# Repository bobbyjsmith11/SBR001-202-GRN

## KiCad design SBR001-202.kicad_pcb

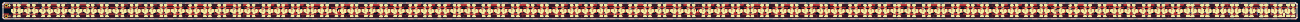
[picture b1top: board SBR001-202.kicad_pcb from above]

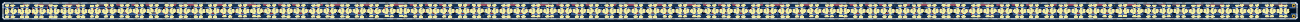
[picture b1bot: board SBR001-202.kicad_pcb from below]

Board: 2 copper layers, 895.4 x 10.9 mm, 1406 parts (703 on the bottom side), 706 nets.

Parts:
D201, D202, D203, D204, D205, D206, D207, D208, D209, D210, D211, D212, D213, D214, D215, D216, D217, D218, D219, D220, D301, D302, D303, D304, D305, D306, D307, D308, D309, D310, D311, D312, D313, D314, D315, D316, D317, D318, D319, D320, D401, D402, D403, D404, D405, D406, D407, D408, D409, D410, D411, D412, D413, D414, D415, D416, D417, D418, D419, D420, D501, D502, D503, D504, D505, D506, D507, D508, D509, D510, D511, D512, D513, D514, D515, D516, D517, D518, D519, D520, D601, D602, D603, D604, D605, D606, D607, D608, D609, D610, D611, D612, D613, D614, D615, D616, D617, D618, D619, D620, D701, D702, D703, D704, D705, D706, D707, D708, D709, D710, D711, D712, D713, D714, D715, D716, D717, D718, D719, D720, D801, D802, D803, D804, D805, D806, D807, D808, D809, D810, D811, D812, D813, D814, D815, D816, D817, D818, D819, D820, D901, D902, D903, D904, D905, D906, D907, D908, D909, D910, D911, D912, D913, D914, D915, D916, D917, D918, D919, D920, D1001, D1002, D1003, D1004, D1005, D1006, D1007, D1008, D1009, D1010, D1011, D1012, D1013, D1015, D1016, D1017, D1101, D1102, D1103, D1104, D1105, D1106, D1107, D1108, D1109, D1110, D1111, D1112, D1113, D1114, D1115, D1116, D1117, D1118, D1119, D1120, D1201, D1202, D1203, D1204, D1205, D1206, D1207, D1208, D1209, D1210, D1211, D1212, D1213, D1214, D1215, D1216, D1217, D1218, D1219, D1220, D1301, D1302, D1303, D1304, D1305, D1306, D1307, D1308, D1309, D1310, D1311, D1312, D1313, D1314, D1315, D1316, D1317, D1318, D1319, D1320, D1401, D1402, D1403, D1404, D1405, D1406, D1407, D1408, D1409, D1410, D1411, D1412, D1413, D1414, D1415, D1416, D1417, D1418, D1419, D1420, D1501, D1502, D1503, D1504, D1505, D1506, D1507, D1508, D1509, D1510, D1511, D1512, D1513, D1514, D1515, D1516, D1517, D1518, D1519, D1520, D1601, D1602, D1603, D1604, D1605, D1606, D1607, D1608, D1609, D1610, D1611, D1612, D1613, D1614, D1615, D1616, D1617, D1618, D1619, D1620, D1701, D1702, D1703, D1704, D1705, D1706, D1707, D1708, D1709, D1710, D1711, D1712, D1713, D1714, D1715, D1716, D1717, D1718, D1719, D1720, D1801, D1802, D1803, D1804, D1805, D1806, D1807, D1808, D1809, D1810, D1811, D1812, D1813, D1814, D1815, D1816, D1817, D1818, D1819, D1820, D1901, D1902, D1903, D1904, D1905, D1906, D1907, D1908, D1909, D1910, D1911, D1912, D1913, D1914, D1915, D1916: GRN; LED_0603
R201, R202, R203, R204, R205, R206, R207, R208, R209, R210, R211, R212, R237, R238, R239, R240, R241, R242, R243, R244, R301, R302, R303, R304, R305, R306, R307, R308, R309, R310, R311, R312, R337, R338, R339, R340, R341, R342, R343, R344, R401, R402, R403, R404, R405, R406, R407, R408, R409, R410, R411, R412, R437, R438, R439, R440, R441, R442, R443, R444, R501, R502, R503, R504, R505, R506, R507, R508, R509, R510, R511, R512, R537, R538, R539, R540, R541, R542, R543, R544, R601, R602, R603, R604, R605, R606, R607, R608, R609, R610, R611, R612, R637, R638, R639, R640, R641, R642, R643, R644, R701, R702, R703, R704, R705, R706, R707, R708, R709, R710, R711, R712, R737, R738, R739, R740, R741, R742, R743, R744, R801, R802, R803, R804, R805, R806, R807, R808, R809, R810, R811, R812, R837, R838, R839, R840, R841, R842, R843, R844, R901, R902, R903, R904, R905, R906, R907, R908, R909, R910, R911, R912, R937, R938, R939, R940, R941, R942, R943, R944, R1001, R1002, R1003, R1004, R1005, R1006, R1007, R1008, R1009, R1010, R1011, R1012, R1037, R1038, R1039, R1040, R1101, R1102, R1103, R1104, R1105, R1106, R1107, R1108, R1109, R1110, R1111, R1112, R1137, R1138, R1139, R1140, R1141, R1142, R1143, R1144, R1201, R1202, R1203, R1204, R1205, R1206, R1207, R1208, R1209, R1210, R1211, R1212, R1237, R1238, R1239, R1240, R1241, R1242, R1243, R1244, R1301, R1302, R1303, R1304, R1305, R1306, R1307, R1308, R1309, R1310, R1311, R1312, R1337, R1338, R1339, R1340, R1341, R1342, R1343, R1344, R1401, R1402, R1403, R1404, R1405, R1406, R1407, R1408, R1409, R1410, R1411, R1412, R1437, R1438, R1439, R1440, R1441, R1442, R1443, R1444, R1501, R1502, R1503, R1504, R1505, R1506, R1507, R1508, R1509, R1510, R1511, R1512, R1537, R1538, R1539, R1540, R1541, R1542, R1543, R1544, R1601, R1602, R1603, R1604, R1605, R1606, R1607, R1608, R1609, R1610, R1611, R1612, R1637, R1638, R1639, R1640, R1641, R1642, R1643, R1644, R1701, R1702, R1703, R1704, R1705, R1706, R1707, R1708, R1709, R1710, R1711, R1712, R1737, R1738, R1739, R1740, R1741, R1742, R1743, R1744, R1801, R1802, R1803, R1804, R1805, R1806, R1807, R1808, R1809, R1810, R1811, R1812, R1837, R1838, R1839, R1840, R1841, R1842, R1843, R1844, R1901, R1902, R1903, R1904, R1905, R1906, R1907, R1908, R1909, R1910, R1911, R1912, R1937, R1938, R1939, R1940: 442; R_0603
R213, R214, R215, R216, R217, R218, R219, R220, R221, R222, R223, R224, R225, R226, R227, R228, R229, R230, R231, R232, R233, R234, R235, R236, R245, R246, R247, R248, R249, R250, R251, R252, R253, R254, R255, R256, R257, R258, R259, R260, R313, R314, R315, R316, R317, R318, R319, R320, R321, R322, R323, R324, R325, R326, R327, R328, R329, R330, R331, R332, R333, R334, R335, R336, R345, R346, R347, R348, R349, R350, R351, R352, R353, R354, R355, R356, R357, R358, R359, R360, R413, R414, R415, R416, R417, R418, R419, R420, R421, R422, R423, R424, R425, R426, R427, R428, R429, R430, R431, R432, R433, R434, R435, R436, R445, R446, R447, R448, R449, R450, R451, R452, R453, R454, R455, R456, R457, R458, R459, R460, R513, R514, R515, R516, R517, R518, R519, R520, R521, R522, R523, R524, R525, R526, R527, R528, R529, R530, R531, R532, R533, R534, R535, R536, R545, R546, R547, R548, R549, R550, R551, R552, R553, R554, R555, R556, R557, R558, R559, R560, R613, R614, R615, R616, R617, R618, R619, R620, R621, R622, R623, R624, R625, R626, R627, R628, R629, R630, R631, R632, R633, R634, R635, R636, R645, R646, R647, R648, R649, R650, R651, R652, R653, R654, R655, R656, R657, R658, R659, R660, R713, R714, R715, R716, R717, R718, R719, R720, R721, R722, R723, R724, R725, R726, R727, R728, R729, R730, R731, R732, R733, R734, R735, R736, R745, R746, R747, R748, R749, R750, R751, R752, R753, R754, R755, R756, R757, R758, R759, R760, R813, R814, R815, R816, R817, R818, R819, R820, R821, R822, R823, R824, R825, R826, R827, R828, R829, R830, R831, R832, R833, R834, R835, R836, R845, R846, R847, R848, R849, R850, R851, R852, R853, R854, R855, R856, R857, R858, R859, R860, R913, R914, R915, R916, R917, R918, R919, R920, R921, R922, R923, R924, R925, R926, R927, R928, R929, R930, R931, R932, R933, R934, R935, R936, R945, R946, R947, R948, R949, R950, R951, R952, R953, R954, R955, R956, R957, R958, R959, R960, R1013, R1014, R1015, R1016, R1017, R1018, R1019, R1020, R1021, R1022, R1023, R1024, R1025, R1026, R1027, R1028, R1029, R1030, R1031, R1032, R1033, R1034, R1035, R1036, R1045, R1046, R1047, R1053, R1054, R1055, R1056, R1113, R1114, R1115, R1116, R1117, R1118, R1119, R1120, R1121, R1122, R1123, R1124, R1125, R1126, R1127, R1128, R1129, R1130, R1131, R1132, R1133, R1134, R1135, R1136, R1145, R1146, R1147, R1148, R1149, R1150, R1151, R1152, R1153, R1154, R1155, R1156, R1157, R1158, R1159, R1160, R1213, R1214, R1215, R1216, R1217, R1218, R1219, R1220, R1221, R1222, R1223, R1224, R1225, R1226, R1227, R1228, R1229, R1230, R1231, R1232, R1233, R1234, R1235, R1236, R1245, R1246, R1247, R1248, R1249, R1250, R1251, R1252, R1253, R1254, R1255, R1256, R1257, R1258, R1259, R1260, R1313, R1314, R1315, R1316, R1317, R1318, R1319, R1320, R1321, R1322, R1323, R1324, R1325, R1326, R1327, R1328, R1329, R1330, R1331, R1332, R1333, R1334, R1335, R1336, R1345, R1346, R1347, R1348, R1349, R1350, R1351, R1352, R1353, R1354, R1355, R1356, R1357, R1358, R1359, R1360, R1413, R1414, R1415, R1416, R1417, R1418, R1419, R1420, R1421, R1422, R1423, R1424, R1425, R1426, R1427, R1428, R1429, R1430, R1431, R1432, R1433, R1434, R1435, R1436, R1445, R1446, R1447, R1448, R1449, R1450, R1451, R1452, R1453, R1454, R1455, R1456, R1457, R1458, R1459, R1460, R1513, R1514, R1515, R1516, R1517, R1518, R1519, R1520, R1521, R1522, R1523, R1524, R1525, R1526, R1527, R1528, R1529, R1530, R1531, R1532, R1533, R1534, R1535, R1536, R1545, R1546, R1547, R1548, R1549, R1550, R1551, R1552, R1553, R1554, R1555, R1556, R1557, R1558, R1559, R1560, R1613, R1614, R1615, R1616, R1617, R1618, R1619, R1620, R1621, R1622, R1623, R1624, R1625, R1626, R1627, R1628, R1629, R1630, R1631, R1632, R1633, R1634, R1635, R1636, R1645, R1646, R1647, R1648, R1649, R1650, R1651, R1652, R1653, R1654, R1655, R1656, R1657, R1658, R1659, R1660, R1713, R1714, R1715, R1716, R1717, R1718, R1719, R1720, R1721, R1722, R1723, R1724, R1725, R1726, R1727, R1728, R1729, R1730, R1731, R1732, R1733, R1734, R1735, R1736, R1745, R1746, R1747, R1748, R1749, R1750, R1751, R1752, R1753, R1754, R1755, R1756, R1757, R1758, R1759, R1760, R1813, R1814, R1815, R1816, R1817, R1818, R1819, R1820, R1821, R1822, R1823, R1824, R1825, R1826, R1827, R1828, R1829, R1830, R1831, R1832, R1833, R1834, R1835, R1836, R1845, R1846, R1847, R1848, R1849, R1850, R1851, R1852, R1853, R1854, R1855, R1856, R1857, R1858, R1859, R1860, R1913, R1914, R1915, R1916, R1917, R1918, R1919, R1920, R1921, R1922, R1923, R1924, R1925, R1926, R1927, R1928, R1929, R1930, R1931, R1932, R1933, R1934, R1935, R1936, R1941, R1942, R1943, R1944, R1945, R1946, R1947: 0; R_0603

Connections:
/Front1/BLOCK_IN: D201.2, R201.2
/Front2/BLOCK_IN: D301.2, R252.1, R301.2
/Front3/BLOCK_IN: D401.2, R352.1, R401.2
/Front4/BLOCK_IN: D501.2, R452.1, R501.2
/Front5/BLOCK_IN: D601.2, R552.1, R601.2
/Front6/BLOCK_IN: D701.2, R652.1, R701.2
/Front7/BLOCK_IN: D801.2, R752.1, R801.2
/Front8/BLOCK_IN: D901.2, R852.1, R901.2
/Front9/BLOCK_IN: D1001.2, R952.1, R1001.2
/Front10/BLOCK_IN: D1101.2, R1101.2
/Front11/BLOCK_IN: D1201.2, R1152.1, R1201.2
/Front12/BLOCK_IN: D1301.2, R1252.1, R1301.2
/Front13/BLOCK_IN: D1401.2, R1352.1, R1401.2
/Front14/BLOCK_IN: D1501.2, R1452.1, R1501.2
/Front15/BLOCK_IN: D1601.2, R1552.1, R1601.2
/Front16/BLOCK_IN: D1701.2, R1652.1, R1701.2
/Front17/BLOCK_IN: D1801.2, R1752.1, R1801.2
/Front18/BLOCK_IN: D1901.2, R1852.1, R1901.2
GND: R225.2, R226.2, R227.2, R228.2, R229.2, R230.2, R231.2, R232.2, R233.2, R234.2, R235.2, R236.2, R253.2, R254.2, R255.2, R256.2, R257.2, R258.2, R259.2, R260.2, R325.2, R326.2, R327.2, R328.2, R329.2, R330.2, R331.2, R332.2, R333.2, R334.2, R335.2, R336.2, R353.2, R354.2, R355.2, R356.2, R357.2, R358.2, R359.2, R360.2, R425.2, R426.2, R427.2, R428.2, R429.2, R430.2, R431.2, R432.2, R433.2, R434.2, R435.2, R436.2, R453.2, R454.2, R455.2, R456.2, R457.2, R458.2, R459.2, R460.2, R525.2, R526.2, R527.2, R528.2, R529.2, R530.2, R531.2, R532.2, R533.2, R534.2, R535.2, R536.2, R553.2, R554.2, R555.2, R556.2, R557.2, R558.2, R559.2, R560.2, R625.2, R626.2, R627.2, R628.2, R629.2, R630.2, R631.2, R632.2, R633.2, R634.2, R635.2, R636.2, R653.2, R654.2, R655.2, R656.2, R657.2, R658.2, R659.2, R660.2, R725.2, R726.2, R727.2, R728.2, R729.2, R730.2, R731.2, R732.2, R733.2, R734.2, R735.2, R736.2, R753.2, R754.2, R755.2, R756.2, R757.2, R758.2, R759.2, R760.2, R825.2, R826.2, R827.2, R828.2, R829.2, R830.2, R831.2, R832.2, R833.2, R834.2, R835.2, R836.2, R853.2, R854.2, R855.2, R856.2, R857.2, R858.2, R859.2, R860.2, R925.2, R926.2, R927.2, R928.2, R929.2, R930.2, R931.2, R932.2, R933.2, R934.2, R935.2, R936.2, R953.2, R954.2, R955.2, R956.2, R957.2, R958.2, R959.2, R960.2, R1025.2, R1026.2, R1027.2, R1028.2, R1029.2, R1030.2, R1031.2, R1032.2, R1033.2, R1034.2, R1035.2, R1036.2, R1053.2, R1054.2, R1055.2, R1056.2, R1125.2, R1126.2, R1127.2, R1128.2, R1129.2, R1130.2, R1131.2, R1132.2, R1133.2, R1134.2, R1135.2, R1136.2, R1153.2, R1154.2, R1155.2, R1156.2, R1157.2, R1158.2, R1159.2, R1160.2, R1225.2, R1226.2, R1227.2, R1228.2, R1229.2, R1230.2, R1231.2, R1232.2, R1233.2, R1234.2, R1235.2, R1236.2, R1253.2, R1254.2, R1255.2, R1256.2, R1257.2, R1258.2, R1259.2, R1260.2, R1325.2, R1326.2, R1327.2, R1328.2, R1329.2, R1330.2, R1331.2, R1332.2, R1333.2, R1334.2, R1335.2, R1336.2, R1353.2, R1354.2, R1355.2, R1356.2, R1357.2, R1358.2, R1359.2, R1360.2, R1425.2, R1426.2, R1427.2, R1428.2, R1429.2, R1430.2, R1431.2, R1432.2, R1433.2, R1434.2, R1435.2, R1436.2, R1453.2, R1454.2, R1455.2, R1456.2, R1457.2, R1458.2, R1459.2, R1460.2, R1525.2, R1526.2, R1527.2, R1528.2, R1529.2, R1530.2, R1531.2, R1532.2, R1533.2, R1534.2, R1535.2, R1536.2, R1553.2, R1554.2, R1555.2, R1556.2, R1557.2, R1558.2, R1559.2, R1560.2, R1625.2, R1626.2, R1627.2, R1628.2, R1629.2, R1630.2, R1631.2, R1632.2, R1633.2, R1634.2, R1635.2, R1636.2, R1653.2, R1654.2, R1655.2, R1656.2, R1657.2, R1658.2, R1659.2, R1660.2, R1725.2, R1726.2, R1727.2, R1728.2, R1729.2, R1730.2, R1731.2, R1732.2, R1733.2, R1734.2, R1735.2, R1736.2, R1753.2, R1754.2, R1755.2, R1756.2, R1757.2, R1758.2, R1759.2, R1760.2, R1825.2, R1826.2, R1827.2, R1828.2, R1829.2, R1830.2, R1831.2, R1832.2, R1833.2, R1834.2, R1835.2, R1836.2, R1853.2, R1854.2, R1855.2, R1856.2, R1857.2, R1858.2, R1859.2, R1860.2, R1925.2, R1926.2, R1927.2, R1928.2, R1929.2, R1930.2, R1931.2, R1932.2, R1933.2, R1934.2, R1935.2, R1936.2, R1944.2, R1945.2, R1946.2, R1947.2
unnamed: D201.1, R213.2, R225.1
unnamed: D202.1, R218.2, R230.1
unnamed: D202.2, R206.2, R217.1
unnamed: D203.1, R222.2, R234.1
unnamed: D203.2, R210.2, R221.1
unnamed: D204.1, R214.2, R226.1
unnamed: D204.2, R202.2, R213.1
unnamed: D205.1, R215.2, R227.1
unnamed: D205.2, R203.2, R214.1
unnamed: D206.1, R216.2, R228.1
unnamed: D206.2, R204.2, R215.1
unnamed: D207.1, R217.2, R229.1
unnamed: D207.2, R205.2, R216.1
unnamed: D208.1, R219.2, R231.1
unnamed: D208.2, R207.2, R218.1
unnamed: D209.1, R220.2, R232.1
unnamed: D209.2, R208.2, R219.1
unnamed: D210.1, R221.2, R233.1
unnamed: D210.2, R209.2, R220.1
unnamed: D211.1, R223.2, R235.1
unnamed: D211.2, R211.2, R222.1
unnamed: D212.1, R224.2, R236.1
unnamed: D212.2, R212.2, R223.1
unnamed: D213.1, R246.2, R254.1
unnamed: D213.2, R238.2, R245.1
unnamed: D214.1, R250.2, R258.1
unnamed: D214.2, R242.2, R249.1
unnamed: D215.1, R245.2, R253.1
unnamed: D215.2, R224.1, R237.2
unnamed: D216.1, R247.2, R255.1
unnamed: D216.2, R239.2, R246.1
unnamed: D217.1, R248.2, R256.1
unnamed: D217.2, R240.2, R247.1
unnamed: D218.1, R249.2, R257.1
unnamed: D218.2, R241.2, R248.1
unnamed: D219.1, R251.2, R259.1
unnamed: D219.2, R243.2, R250.1
unnamed: D220.1, R252.2, R260.1
unnamed: D220.2, R244.2, R251.1
unnamed: D301.1, R313.2, R325.1
unnamed: D302.1, R318.2, R330.1
unnamed: D302.2, R306.2, R317.1
unnamed: D303.1, R322.2, R334.1
unnamed: D303.2, R310.2, R321.1
unnamed: D304.1, R314.2, R326.1
unnamed: D304.2, R302.2, R313.1
unnamed: D305.1, R315.2, R327.1
unnamed: D305.2, R303.2, R314.1
unnamed: D306.1, R316.2, R328.1
unnamed: D306.2, R304.2, R315.1
unnamed: D307.1, R317.2, R329.1
unnamed: D307.2, R305.2, R316.1
unnamed: D308.1, R319.2, R331.1
unnamed: D308.2, R307.2, R318.1
unnamed: D309.1, R320.2, R332.1
unnamed: D309.2, R308.2, R319.1
unnamed: D310.1, R321.2, R333.1
unnamed: D310.2, R309.2, R320.1
unnamed: D311.1, R323.2, R335.1
unnamed: D311.2, R311.2, R322.1
unnamed: D312.1, R324.2, R336.1
unnamed: D312.2, R312.2, R323.1
unnamed: D313.1, R346.2, R354.1
unnamed: D313.2, R338.2, R345.1
unnamed: D314.1, R350.2, R358.1
unnamed: D314.2, R342.2, R349.1
unnamed: D315.1, R345.2, R353.1
unnamed: D315.2, R324.1, R337.2
unnamed: D316.1, R347.2, R355.1
unnamed: D316.2, R339.2, R346.1
unnamed: D317.1, R348.2, R356.1
unnamed: D317.2, R340.2, R347.1
unnamed: D318.1, R349.2, R357.1
unnamed: D318.2, R341.2, R348.1
unnamed: D319.1, R351.2, R359.1
unnamed: D319.2, R343.2, R350.1
unnamed: D320.1, R352.2, R360.1
unnamed: D320.2, R344.2, R351.1
unnamed: D401.1, R413.2, R425.1
unnamed: D402.1, R418.2, R430.1
unnamed: D402.2, R406.2, R417.1
unnamed: D403.1, R422.2, R434.1
unnamed: D403.2, R410.2, R421.1
unnamed: D404.1, R414.2, R426.1
unnamed: D404.2, R402.2, R413.1
unnamed: D405.1, R415.2, R427.1
unnamed: D405.2, R403.2, R414.1
unnamed: D406.1, R416.2, R428.1
unnamed: D406.2, R404.2, R415.1
unnamed: D407.1, R417.2, R429.1
unnamed: D407.2, R405.2, R416.1
unnamed: D408.1, R419.2, R431.1
unnamed: D408.2, R407.2, R418.1
unnamed: D409.1, R420.2, R432.1
unnamed: D409.2, R408.2, R419.1
unnamed: D410.1, R421.2, R433.1
unnamed: D410.2, R409.2, R420.1
unnamed: D411.1, R423.2, R435.1
unnamed: D411.2, R411.2, R422.1
unnamed: D412.1, R424.2, R436.1
unnamed: D412.2, R412.2, R423.1
unnamed: D413.1, R446.2, R454.1
unnamed: D413.2, R438.2, R445.1
unnamed: D414.1, R450.2, R458.1
unnamed: D414.2, R442.2, R449.1
unnamed: D415.1, R445.2, R453.1
unnamed: D415.2, R424.1, R437.2
unnamed: D416.1, R447.2, R455.1
unnamed: D416.2, R439.2, R446.1
unnamed: D417.1, R448.2, R456.1
unnamed: D417.2, R440.2, R447.1
unnamed: D418.1, R449.2, R457.1
unnamed: D418.2, R441.2, R448.1
unnamed: D419.1, R451.2, R459.1
unnamed: D419.2, R443.2, R450.1
unnamed: D420.1, R452.2, R460.1
unnamed: D420.2, R444.2, R451.1
unnamed: D501.1, R513.2, R525.1
unnamed: D502.1, R518.2, R530.1
unnamed: D502.2, R506.2, R517.1
unnamed: D503.1, R522.2, R534.1
unnamed: D503.2, R510.2, R521.1
unnamed: D504.1, R514.2, R526.1
unnamed: D504.2, R502.2, R513.1
unnamed: D505.1, R515.2, R527.1
unnamed: D505.2, R503.2, R514.1
unnamed: D506.1, R516.2, R528.1
unnamed: D506.2, R504.2, R515.1
unnamed: D507.1, R517.2, R529.1
unnamed: D507.2, R505.2, R516.1
unnamed: D508.1, R519.2, R531.1
unnamed: D508.2, R507.2, R518.1
unnamed: D509.1, R520.2, R532.1
unnamed: D509.2, R508.2, R519.1
unnamed: D510.1, R521.2, R533.1
unnamed: D510.2, R509.2, R520.1
unnamed: D511.1, R523.2, R535.1
unnamed: D511.2, R511.2, R522.1
unnamed: D512.1, R524.2, R536.1
unnamed: D512.2, R512.2, R523.1
unnamed: D513.1, R546.2, R554.1
unnamed: D513.2, R538.2, R545.1
unnamed: D514.1, R550.2, R558.1
unnamed: D514.2, R542.2, R549.1
unnamed: D515.1, R545.2, R553.1
unnamed: D515.2, R524.1, R537.2
unnamed: D516.1, R547.2, R555.1
unnamed: D516.2, R539.2, R546.1
unnamed: D517.1, R548.2, R556.1
unnamed: D517.2, R540.2, R547.1
unnamed: D518.1, R549.2, R557.1
unnamed: D518.2, R541.2, R548.1
unnamed: D519.1, R551.2, R559.1
unnamed: D519.2, R543.2, R550.1
unnamed: D520.1, R552.2, R560.1
unnamed: D520.2, R544.2, R551.1
unnamed: D601.1, R613.2, R625.1
unnamed: D602.1, R618.2, R630.1
unnamed: D602.2, R606.2, R617.1
unnamed: D603.1, R622.2, R634.1
unnamed: D603.2, R610.2, R621.1
unnamed: D604.1, R614.2, R626.1
unnamed: D604.2, R602.2, R613.1
unnamed: D605.1, R615.2, R627.1
unnamed: D605.2, R603.2, R614.1
unnamed: D606.1, R616.2, R628.1
unnamed: D606.2, R604.2, R615.1
unnamed: D607.1, R617.2, R629.1
unnamed: D607.2, R605.2, R616.1
unnamed: D608.1, R619.2, R631.1
unnamed: D608.2, R607.2, R618.1
unnamed: D609.1, R620.2, R632.1
unnamed: D609.2, R608.2, R619.1
unnamed: D610.1, R621.2, R633.1
unnamed: D610.2, R609.2, R620.1
unnamed: D611.1, R623.2, R635.1
unnamed: D611.2, R611.2, R622.1
unnamed: D612.1, R624.2, R636.1
unnamed: D612.2, R612.2, R623.1
unnamed: D613.1, R646.2, R654.1
unnamed: D613.2, R638.2, R645.1
unnamed: D614.1, R650.2, R658.1
unnamed: D614.2, R642.2, R649.1
unnamed: D615.1, R645.2, R653.1
unnamed: D615.2, R624.1, R637.2
unnamed: D616.1, R647.2, R655.1
unnamed: D616.2, R639.2, R646.1
unnamed: D617.1, R648.2, R656.1
unnamed: D617.2, R640.2, R647.1
unnamed: D618.1, R649.2, R657.1
unnamed: D618.2, R641.2, R648.1
unnamed: D619.1, R651.2, R659.1
unnamed: D619.2, R643.2, R650.1
unnamed: D620.1, R652.2, R660.1
unnamed: D620.2, R644.2, R651.1
unnamed: D701.1, R713.2, R725.1
unnamed: D702.1, R718.2, R730.1
unnamed: D702.2, R706.2, R717.1
unnamed: D703.1, R722.2, R734.1
unnamed: D703.2, R710.2, R721.1
unnamed: D704.1, R714.2, R726.1
unnamed: D704.2, R702.2, R713.1
unnamed: D705.1, R715.2, R727.1
unnamed: D705.2, R703.2, R714.1
unnamed: D706.1, R716.2, R728.1
unnamed: D706.2, R704.2, R715.1
unnamed: D707.1, R717.2, R729.1
unnamed: D707.2, R705.2, R716.1
unnamed: D708.1, R719.2, R731.1
unnamed: D708.2, R707.2, R718.1
unnamed: D709.1, R720.2, R732.1
unnamed: D709.2, R708.2, R719.1
unnamed: D710.1, R721.2, R733.1
unnamed: D710.2, R709.2, R720.1
unnamed: D711.1, R723.2, R735.1
unnamed: D711.2, R711.2, R722.1
unnamed: D712.1, R724.2, R736.1
unnamed: D712.2, R712.2, R723.1
unnamed: D713.1, R746.2, R754.1
unnamed: D713.2, R738.2, R745.1
unnamed: D714.1, R750.2, R758.1
unnamed: D714.2, R742.2, R749.1
unnamed: D715.1, R745.2, R753.1
unnamed: D715.2, R724.1, R737.2
unnamed: D716.1, R747.2, R755.1
unnamed: D716.2, R739.2, R746.1
unnamed: D717.1, R748.2, R756.1
unnamed: D717.2, R740.2, R747.1
unnamed: D718.1, R749.2, R757.1
unnamed: D718.2, R741.2, R748.1
unnamed: D719.1, R751.2, R759.1
unnamed: D719.2, R743.2, R750.1
unnamed: D720.1, R752.2, R760.1
unnamed: D720.2, R744.2, R751.1
unnamed: D801.1, R813.2, R825.1
unnamed: D802.1, R818.2, R830.1
unnamed: D802.2, R806.2, R817.1
unnamed: D803.1, R822.2, R834.1
unnamed: D803.2, R810.2, R821.1
unnamed: D804.1, R814.2, R826.1
unnamed: D804.2, R802.2, R813.1
unnamed: D805.1, R815.2, R827.1
unnamed: D805.2, R803.2, R814.1
unnamed: D806.1, R816.2, R828.1
unnamed: D806.2, R804.2, R815.1
unnamed: D807.1, R817.2, R829.1
unnamed: D807.2, R805.2, R816.1
unnamed: D808.1, R819.2, R831.1
unnamed: D808.2, R807.2, R818.1
unnamed: D809.1, R820.2, R832.1
unnamed: D809.2, R808.2, R819.1
unnamed: D810.1, R821.2, R833.1
unnamed: D810.2, R809.2, R820.1
unnamed: D811.1, R823.2, R835.1
unnamed: D811.2, R811.2, R822.1
unnamed: D812.1, R824.2, R836.1
unnamed: D812.2, R812.2, R823.1
unnamed: D813.1, R846.2, R854.1
unnamed: D813.2, R838.2, R845.1
unnamed: D814.1, R850.2, R858.1
unnamed: D814.2, R842.2, R849.1
unnamed: D815.1, R845.2, R853.1
unnamed: D815.2, R824.1, R837.2
unnamed: D816.1, R847.2, R855.1
unnamed: D816.2, R839.2, R846.1
unnamed: D817.1, R848.2, R856.1
unnamed: D817.2, R840.2, R847.1
unnamed: D818.1, R849.2, R857.1
unnamed: D818.2, R841.2, R848.1
unnamed: D819.1, R851.2, R859.1
unnamed: D819.2, R843.2, R850.1
unnamed: D820.1, R852.2, R860.1
unnamed: D820.2, R844.2, R851.1
unnamed: D901.1, R913.2, R925.1
unnamed: D902.1, R918.2, R930.1
unnamed: D902.2, R906.2, R917.1
unnamed: D903.1, R922.2, R934.1
unnamed: D903.2, R910.2, R921.1
unnamed: D904.1, R914.2, R926.1
unnamed: D904.2, R902.2, R913.1
unnamed: D905.1, R915.2, R927.1
unnamed: D905.2, R903.2, R914.1
unnamed: D906.1, R916.2, R928.1
unnamed: D906.2, R904.2, R915.1
unnamed: D907.1, R917.2, R929.1
unnamed: D907.2, R905.2, R916.1
unnamed: D908.1, R919.2, R931.1
unnamed: D908.2, R907.2, R918.1
unnamed: D909.1, R920.2, R932.1
unnamed: D909.2, R908.2, R919.1
unnamed: D910.1, R921.2, R933.1
unnamed: D910.2, R909.2, R920.1
unnamed: D911.1, R923.2, R935.1
unnamed: D911.2, R911.2, R922.1
unnamed: D912.1, R924.2, R936.1
unnamed: D912.2, R912.2, R923.1
unnamed: D913.1, R946.2, R954.1
unnamed: D913.2, R938.2, R945.1
unnamed: D914.1, R950.2, R958.1
unnamed: D914.2, R942.2, R949.1
unnamed: D915.1, R945.2, R953.1
unnamed: D915.2, R924.1, R937.2
unnamed: D916.1, R947.2, R955.1
unnamed: D916.2, R939.2, R946.1
unnamed: D917.1, R948.2, R956.1
unnamed: D917.2, R940.2, R947.1
unnamed: D918.1, R949.2, R957.1
unnamed: D918.2, R941.2, R948.1
unnamed: D919.1, R951.2, R959.1
unnamed: D919.2, R943.2, R950.1
unnamed: D920.1, R952.2, R960.1
unnamed: D920.2, R944.2, R951.1
unnamed: D1001.1, R1013.2, R1025.1
unnamed: D1002.1, R1018.2, R1030.1
unnamed: D1002.2, R1006.2, R1017.1
unnamed: D1003.1, R1022.2, R1034.1
unnamed: D1003.2, R1010.2, R1021.1
unnamed: D1004.1, R1014.2, R1026.1
unnamed: D1004.2, R1002.2, R1013.1
unnamed: D1005.1, R1015.2, R1027.1
unnamed: D1005.2, R1003.2, R1014.1
unnamed: D1006.1, R1016.2, R1028.1
unnamed: D1006.2, R1004.2, R1015.1
unnamed: D1007.1, R1017.2, R1029.1
unnamed: D1007.2, R1005.2, R1016.1
unnamed: D1008.1, R1019.2, R1031.1
unnamed: D1008.2, R1007.2, R1018.1
unnamed: D1009.1, R1020.2, R1032.1
unnamed: D1009.2, R1008.2, R1019.1
unnamed: D1010.1, R1021.2, R1033.1
unnamed: D1010.2, R1009.2, R1020.1
unnamed: D1011.1, R1023.2, R1035.1
unnamed: D1011.2, R1011.2, R1022.1
unnamed: D1012.1, R1024.2, R1036.1
unnamed: D1012.2, R1012.2, R1023.1
unnamed: D1013.1, R1046.2, R1054.1
unnamed: D1013.2, R1038.2, R1045.1
unnamed: D1015.1, R1045.2, R1053.1
unnamed: D1015.2, R1024.1, R1037.2
unnamed: D1016.1, R1047.2, R1055.1
unnamed: D1016.2, R1039.2, R1046.1
unnamed: D1017.1, R1056.1
unnamed: D1017.2, R1040.2, R1047.1
unnamed: D1101.1, R1113.2, R1125.1
unnamed: D1102.1, R1118.2, R1130.1
unnamed: D1102.2, R1106.2, R1117.1
unnamed: D1103.1, R1122.2, R1134.1
unnamed: D1103.2, R1110.2, R1121.1
unnamed: D1104.1, R1114.2, R1126.1
unnamed: D1104.2, R1102.2, R1113.1
unnamed: D1105.1, R1115.2, R1127.1
unnamed: D1105.2, R1103.2, R1114.1
unnamed: D1106.1, R1116.2, R1128.1
unnamed: D1106.2, R1104.2, R1115.1
unnamed: D1107.1, R1117.2, R1129.1
unnamed: D1107.2, R1105.2, R1116.1
unnamed: D1108.1, R1119.2, R1131.1
unnamed: D1108.2, R1107.2, R1118.1
unnamed: D1109.1, R1120.2, R1132.1
unnamed: D1109.2, R1108.2, R1119.1
unnamed: D1110.1, R1121.2, R1133.1
unnamed: D1110.2, R1109.2, R1120.1
unnamed: D1111.1, R1123.2, R1135.1
unnamed: D1111.2, R1111.2, R1122.1
unnamed: D1112.1, R1124.2, R1136.1
unnamed: D1112.2, R1112.2, R1123.1
unnamed: D1113.1, R1146.2, R1154.1
unnamed: D1113.2, R1138.2, R1145.1
unnamed: D1114.1, R1150.2, R1158.1
unnamed: D1114.2, R1142.2, R1149.1
unnamed: D1115.1, R1145.2, R1153.1
unnamed: D1115.2, R1124.1, R1137.2
unnamed: D1116.1, R1147.2, R1155.1
unnamed: D1116.2, R1139.2, R1146.1
unnamed: D1117.1, R1148.2, R1156.1
unnamed: D1117.2, R1140.2, R1147.1
unnamed: D1118.1, R1149.2, R1157.1
unnamed: D1118.2, R1141.2, R1148.1
unnamed: D1119.1, R1151.2, R1159.1
unnamed: D1119.2, R1143.2, R1150.1
unnamed: D1120.1, R1152.2, R1160.1
unnamed: D1120.2, R1144.2, R1151.1
unnamed: D1201.1, R1213.2, R1225.1
unnamed: D1202.1, R1218.2, R1230.1
unnamed: D1202.2, R1206.2, R1217.1
unnamed: D1203.1, R1222.2, R1234.1
unnamed: D1203.2, R1210.2, R1221.1
unnamed: D1204.1, R1214.2, R1226.1
unnamed: D1204.2, R1202.2, R1213.1
unnamed: D1205.1, R1215.2, R1227.1
unnamed: D1205.2, R1203.2, R1214.1
unnamed: D1206.1, R1216.2, R1228.1
unnamed: D1206.2, R1204.2, R1215.1
unnamed: D1207.1, R1217.2, R1229.1
unnamed: D1207.2, R1205.2, R1216.1
unnamed: D1208.1, R1219.2, R1231.1
unnamed: D1208.2, R1207.2, R1218.1
unnamed: D1209.1, R1220.2, R1232.1
unnamed: D1209.2, R1208.2, R1219.1
unnamed: D1210.1, R1221.2, R1233.1
unnamed: D1210.2, R1209.2, R1220.1
unnamed: D1211.1, R1223.2, R1235.1
unnamed: D1211.2, R1211.2, R1222.1
unnamed: D1212.1, R1224.2, R1236.1
unnamed: D1212.2, R1212.2, R1223.1
unnamed: D1213.1, R1246.2, R1254.1
unnamed: D1213.2, R1238.2, R1245.1
unnamed: D1214.1, R1250.2, R1258.1
unnamed: D1214.2, R1242.2, R1249.1
unnamed: D1215.1, R1245.2, R1253.1
unnamed: D1215.2, R1224.1, R1237.2
unnamed: D1216.1, R1247.2, R1255.1
unnamed: D1216.2, R1239.2, R1246.1
unnamed: D1217.1, R1248.2, R1256.1
unnamed: D1217.2, R1240.2, R1247.1
unnamed: D1218.1, R1249.2, R1257.1
unnamed: D1218.2, R1241.2, R1248.1
unnamed: D1219.1, R1251.2, R1259.1
unnamed: D1219.2, R1243.2, R1250.1
unnamed: D1220.1, R1252.2, R1260.1
unnamed: D1220.2, R1244.2, R1251.1
unnamed: D1301.1, R1313.2, R1325.1
unnamed: D1302.1, R1318.2, R1330.1
unnamed: D1302.2, R1306.2, R1317.1
unnamed: D1303.1, R1322.2, R1334.1
unnamed: D1303.2, R1310.2, R1321.1
unnamed: D1304.1, R1314.2, R1326.1
unnamed: D1304.2, R1302.2, R1313.1
unnamed: D1305.1, R1315.2, R1327.1
unnamed: D1305.2, R1303.2, R1314.1
unnamed: D1306.1, R1316.2, R1328.1
unnamed: D1306.2, R1304.2, R1315.1
unnamed: D1307.1, R1317.2, R1329.1
unnamed: D1307.2, R1305.2, R1316.1
unnamed: D1308.1, R1319.2, R1331.1
unnamed: D1308.2, R1307.2, R1318.1
unnamed: D1309.1, R1320.2, R1332.1
unnamed: D1309.2, R1308.2, R1319.1
unnamed: D1310.1, R1321.2, R1333.1
unnamed: D1310.2, R1309.2, R1320.1
unnamed: D1311.1, R1323.2, R1335.1
unnamed: D1311.2, R1311.2, R1322.1
unnamed: D1312.1, R1324.2, R1336.1
unnamed: D1312.2, R1312.2, R1323.1
unnamed: D1313.1, R1346.2, R1354.1
unnamed: D1313.2, R1338.2, R1345.1
unnamed: D1314.1, R1350.2, R1358.1
unnamed: D1314.2, R1342.2, R1349.1
unnamed: D1315.1, R1345.2, R1353.1
unnamed: D1315.2, R1324.1, R1337.2
unnamed: D1316.1, R1347.2, R1355.1
unnamed: D1316.2, R1339.2, R1346.1
unnamed: D1317.1, R1348.2, R1356.1
unnamed: D1317.2, R1340.2, R1347.1
unnamed: D1318.1, R1349.2, R1357.1
unnamed: D1318.2, R1341.2, R1348.1
unnamed: D1319.1, R1351.2, R1359.1
unnamed: D1319.2, R1343.2, R1350.1
unnamed: D1320.1, R1352.2, R1360.1
unnamed: D1320.2, R1344.2, R1351.1
unnamed: D1401.1, R1413.2, R1425.1
unnamed: D1402.1, R1418.2, R1430.1
unnamed: D1402.2, R1406.2, R1417.1
unnamed: D1403.1, R1422.2, R1434.1
unnamed: D1403.2, R1410.2, R1421.1
unnamed: D1404.1, R1414.2, R1426.1
unnamed: D1404.2, R1402.2, R1413.1
unnamed: D1405.1, R1415.2, R1427.1
unnamed: D1405.2, R1403.2, R1414.1
unnamed: D1406.1, R1416.2, R1428.1
unnamed: D1406.2, R1404.2, R1415.1
unnamed: D1407.1, R1417.2, R1429.1
unnamed: D1407.2, R1405.2, R1416.1
unnamed: D1408.1, R1419.2, R1431.1
unnamed: D1408.2, R1407.2, R1418.1
unnamed: D1409.1, R1420.2, R1432.1
unnamed: D1409.2, R1408.2, R1419.1
unnamed: D1410.1, R1421.2, R1433.1
unnamed: D1410.2, R1409.2, R1420.1
unnamed: D1411.1, R1423.2, R1435.1
unnamed: D1411.2, R1411.2, R1422.1
unnamed: D1412.1, R1424.2, R1436.1
unnamed: D1412.2, R1412.2, R1423.1
unnamed: D1413.1, R1446.2, R1454.1
unnamed: D1413.2, R1438.2, R1445.1
unnamed: D1414.1, R1450.2, R1458.1
unnamed: D1414.2, R1442.2, R1449.1
unnamed: D1415.1, R1445.2, R1453.1
unnamed: D1415.2, R1424.1, R1437.2
unnamed: D1416.1, R1447.2, R1455.1
unnamed: D1416.2, R1439.2, R1446.1
unnamed: D1417.1, R1448.2, R1456.1
unnamed: D1417.2, R1440.2, R1447.1
unnamed: D1418.1, R1449.2, R1457.1
unnamed: D1418.2, R1441.2, R1448.1
unnamed: D1419.1, R1451.2, R1459.1
unnamed: D1419.2, R1443.2, R1450.1
unnamed: D1420.1, R1452.2, R1460.1
unnamed: D1420.2, R1444.2, R1451.1
unnamed: D1501.1, R1513.2, R1525.1
unnamed: D1502.1, R1518.2, R1530.1
unnamed: D1502.2, R1506.2, R1517.1
unnamed: D1503.1, R1522.2, R1534.1
unnamed: D1503.2, R1510.2, R1521.1
unnamed: D1504.1, R1514.2, R1526.1
unnamed: D1504.2, R1502.2, R1513.1
unnamed: D1505.1, R1515.2, R1527.1
unnamed: D1505.2, R1503.2, R1514.1
unnamed: D1506.1, R1516.2, R1528.1
unnamed: D1506.2, R1504.2, R1515.1
unnamed: D1507.1, R1517.2, R1529.1
unnamed: D1507.2, R1505.2, R1516.1
unnamed: D1508.1, R1519.2, R1531.1
unnamed: D1508.2, R1507.2, R1518.1
unnamed: D1509.1, R1520.2, R1532.1
unnamed: D1509.2, R1508.2, R1519.1
unnamed: D1510.1, R1521.2, R1533.1
unnamed: D1510.2, R1509.2, R1520.1
unnamed: D1511.1, R1523.2, R1535.1
unnamed: D1511.2, R1511.2, R1522.1
unnamed: D1512.1, R1524.2, R1536.1
unnamed: D1512.2, R1512.2, R1523.1
unnamed: D1513.1, R1546.2, R1554.1
unnamed: D1513.2, R1538.2, R1545.1
unnamed: D1514.1, R1550.2, R1558.1
unnamed: D1514.2, R1542.2, R1549.1
unnamed: D1515.1, R1545.2, R1553.1
unnamed: D1515.2, R1524.1, R1537.2
unnamed: D1516.1, R1547.2, R1555.1
unnamed: D1516.2, R1539.2, R1546.1
unnamed: D1517.1, R1548.2, R1556.1
unnamed: D1517.2, R1540.2, R1547.1
unnamed: D1518.1, R1549.2, R1557.1
unnamed: D1518.2, R1541.2, R1548.1
unnamed: D1519.1, R1551.2, R1559.1
unnamed: D1519.2, R1543.2, R1550.1
unnamed: D1520.1, R1552.2, R1560.1
unnamed: D1520.2, R1544.2, R1551.1
unnamed: D1601.1, R1613.2, R1625.1
unnamed: D1602.1, R1618.2, R1630.1
unnamed: D1602.2, R1606.2, R1617.1
unnamed: D1603.1, R1622.2, R1634.1
unnamed: D1603.2, R1610.2, R1621.1
unnamed: D1604.1, R1614.2, R1626.1
unnamed: D1604.2, R1602.2, R1613.1
unnamed: D1605.1, R1615.2, R1627.1
unnamed: D1605.2, R1603.2, R1614.1
unnamed: D1606.1, R1616.2, R1628.1
unnamed: D1606.2, R1604.2, R1615.1
unnamed: D1607.1, R1617.2, R1629.1
unnamed: D1607.2, R1605.2, R1616.1
unnamed: D1608.1, R1619.2, R1631.1
unnamed: D1608.2, R1607.2, R1618.1
unnamed: D1609.1, R1620.2, R1632.1
unnamed: D1609.2, R1608.2, R1619.1
unnamed: D1610.1, R1621.2, R1633.1
unnamed: D1610.2, R1609.2, R1620.1
unnamed: D1611.1, R1623.2, R1635.1
unnamed: D1611.2, R1611.2, R1622.1
unnamed: D1612.1, R1624.2, R1636.1
unnamed: D1612.2, R1612.2, R1623.1
unnamed: D1613.1, R1646.2, R1654.1
unnamed: D1613.2, R1638.2, R1645.1
unnamed: D1614.1, R1650.2, R1658.1
unnamed: D1614.2, R1642.2, R1649.1
unnamed: D1615.1, R1645.2, R1653.1
unnamed: D1615.2, R1624.1, R1637.2
unnamed: D1616.1, R1647.2, R1655.1
unnamed: D1616.2, R1639.2, R1646.1
unnamed: D1617.1, R1648.2, R1656.1
unnamed: D1617.2, R1640.2, R1647.1
unnamed: D1618.1, R1649.2, R1657.1
unnamed: D1618.2, R1641.2, R1648.1
unnamed: D1619.1, R1651.2, R1659.1
unnamed: D1619.2, R1643.2, R1650.1
unnamed: D1620.1, R1652.2, R1660.1
unnamed: D1620.2, R1644.2, R1651.1
unnamed: D1701.1, R1713.2, R1725.1
unnamed: D1702.1, R1718.2, R1730.1
unnamed: D1702.2, R1706.2, R1717.1
unnamed: D1703.1, R1722.2, R1734.1
unnamed: D1703.2, R1710.2, R1721.1
unnamed: D1704.1, R1714.2, R1726.1
unnamed: D1704.2, R1702.2, R1713.1
unnamed: D1705.1, R1715.2, R1727.1
unnamed: D1705.2, R1703.2, R1714.1
unnamed: D1706.1, R1716.2, R1728.1
unnamed: D1706.2, R1704.2, R1715.1
unnamed: D1707.1, R1717.2, R1729.1
unnamed: D1707.2, R1705.2, R1716.1
unnamed: D1708.1, R1719.2, R1731.1
unnamed: D1708.2, R1707.2, R1718.1
unnamed: D1709.1, R1720.2, R1732.1
unnamed: D1709.2, R1708.2, R1719.1
unnamed: D1710.1, R1721.2, R1733.1
unnamed: D1710.2, R1709.2, R1720.1
unnamed: D1711.1, R1723.2, R1735.1
unnamed: D1711.2, R1711.2, R1722.1
unnamed: D1712.1, R1724.2, R1736.1
unnamed: D1712.2, R1712.2, R1723.1
unnamed: D1713.1, R1746.2, R1754.1
unnamed: D1713.2, R1738.2, R1745.1
unnamed: D1714.1, R1750.2, R1758.1
unnamed: D1714.2, R1742.2, R1749.1
unnamed: D1715.1, R1745.2, R1753.1
unnamed: D1715.2, R1724.1, R1737.2
unnamed: D1716.1, R1747.2, R1755.1
unnamed: D1716.2, R1739.2, R1746.1
unnamed: D1717.1, R1748.2, R1756.1
unnamed: D1717.2, R1740.2, R1747.1
unnamed: D1718.1, R1749.2, R1757.1
unnamed: D1718.2, R1741.2, R1748.1
unnamed: D1719.1, R1751.2, R1759.1
unnamed: D1719.2, R1743.2, R1750.1
unnamed: D1720.1, R1752.2, R1760.1
unnamed: D1720.2, R1744.2, R1751.1
unnamed: D1801.1, R1813.2, R1825.1
unnamed: D1802.1, R1818.2, R1830.1
unnamed: D1802.2, R1806.2, R1817.1
unnamed: D1803.1, R1822.2, R1834.1
unnamed: D1803.2, R1810.2, R1821.1
unnamed: D1804.1, R1814.2, R1826.1
unnamed: D1804.2, R1802.2, R1813.1
unnamed: D1805.1, R1815.2, R1827.1
unnamed: D1805.2, R1803.2, R1814.1
unnamed: D1806.1, R1816.2, R1828.1
unnamed: D1806.2, R1804.2, R1815.1
unnamed: D1807.1, R1817.2, R1829.1
unnamed: D1807.2, R1805.2, R1816.1
unnamed: D1808.1, R1819.2, R1831.1
unnamed: D1808.2, R1807.2, R1818.1
unnamed: D1809.1, R1820.2, R1832.1
unnamed: D1809.2, R1808.2, R1819.1
unnamed: D1810.1, R1821.2, R1833.1
unnamed: D1810.2, R1809.2, R1820.1
unnamed: D1811.1, R1823.2, R1835.1
unnamed: D1811.2, R1811.2, R1822.1
unnamed: D1812.1, R1824.2, R1836.1
unnamed: D1812.2, R1812.2, R1823.1
unnamed: D1813.1, R1846.2, R1854.1
unnamed: D1813.2, R1838.2, R1845.1
unnamed: D1814.1, R1850.2, R1858.1
unnamed: D1814.2, R1842.2, R1849.1
unnamed: D1815.1, R1845.2, R1853.1
unnamed: D1815.2, R1824.1, R1837.2
unnamed: D1816.1, R1847.2, R1855.1
unnamed: D1816.2, R1839.2, R1846.1
unnamed: D1817.1, R1848.2, R1856.1
unnamed: D1817.2, R1840.2, R1847.1
unnamed: D1818.1, R1849.2, R1857.1
unnamed: D1818.2, R1841.2, R1848.1
unnamed: D1819.1, R1851.2, R1859.1
unnamed: D1819.2, R1843.2, R1850.1
unnamed: D1820.1, R1852.2, R1860.1
unnamed: D1820.2, R1844.2, R1851.1
unnamed: D1901.1, R1913.2, R1925.1
unnamed: D1902.1, R1918.2, R1930.1
unnamed: D1902.2, R1906.2, R1917.1
unnamed: D1903.1, R1922.2, R1934.1
unnamed: D1903.2, R1910.2, R1921.1
unnamed: D1904.1, R1914.2, R1926.1
unnamed: D1904.2, R1902.2, R1913.1
unnamed: D1905.1, R1915.2, R1927.1
unnamed: D1905.2, R1903.2, R1914.1
unnamed: D1906.1, R1916.2, R1928.1
unnamed: D1906.2, R1904.2, R1915.1
unnamed: D1907.1, R1917.2, R1929.1
unnamed: D1907.2, R1905.2, R1916.1
unnamed: D1908.1, R1919.2, R1931.1
unnamed: D1908.2, R1907.2, R1918.1
unnamed: D1909.1, R1920.2, R1932.1
unnamed: D1909.2, R1908.2, R1919.1
unnamed: D1910.1, R1921.2, R1933.1
unnamed: D1910.2, R1909.2, R1920.1
unnamed: D1911.1, R1923.2, R1935.1
unnamed: D1911.2, R1911.2, R1922.1
unnamed: D1912.1, R1924.2, R1936.1
unnamed: D1912.2, R1912.2, R1923.1
unnamed: D1913.1, R1942.2, R1945.1
unnamed: D1913.2, R1938.2, R1941.1
unnamed: D1914.1, R1941.2, R1944.1
unnamed: D1914.2, R1924.1, R1937.2
unnamed: D1915.1, R1943.2, R1946.1
unnamed: D1915.2, R1939.2, R1942.1
unnamed: D1916.1, R1947.1
unnamed: D1916.2, R1940.2, R1943.1
VDD: R201.1, R202.1, R203.1, R204.1, R205.1, R206.1, R207.1, R208.1, R209.1, R210.1, R211.1, R212.1, R237.1, R238.1, R239.1, R240.1, R241.1, R242.1, R243.1, R244.1, R301.1, R302.1, R303.1, R304.1, R305.1, R306.1, R307.1, R308.1, R309.1, R310.1, R311.1, R312.1, R337.1, R338.1, R339.1, R340.1, R341.1, R342.1, R343.1, R344.1, R401.1, R402.1, R403.1, R404.1, R405.1, R406.1, R407.1, R408.1, R409.1, R410.1, R411.1, R412.1, R437.1, R438.1, R439.1, R440.1, R441.1, R442.1, R443.1, R444.1, R501.1, R502.1, R503.1, R504.1, R505.1, R506.1, R507.1, R508.1, R509.1, R510.1, R511.1, R512.1, R537.1, R538.1, R539.1, R540.1, R541.1, R542.1, R543.1, R544.1, R601.1, R602.1, R603.1, R604.1, R605.1, R606.1, R607.1, R608.1, R609.1, R610.1, R611.1, R612.1, R637.1, R638.1, R639.1, R640.1, R641.1, R642.1, R643.1, R644.1, R701.1, R702.1, R703.1, R704.1, R705.1, R706.1, R707.1, R708.1, R709.1, R710.1, R711.1, R712.1, R737.1, R738.1, R739.1, R740.1, R741.1, R742.1, R743.1, R744.1, R801.1, R802.1, R803.1, R804.1, R805.1, R806.1, R807.1, R808.1, R809.1, R810.1, R811.1, R812.1, R837.1, R838.1, R839.1, R840.1, R841.1, R842.1, R843.1, R844.1, R901.1, R902.1, R903.1, R904.1, R905.1, R906.1, R907.1, R908.1, R909.1, R910.1, R911.1, R912.1, R937.1, R938.1, R939.1, R940.1, R941.1, R942.1, R943.1, R944.1, R1001.1, R1002.1, R1003.1, R1004.1, R1005.1, R1006.1, R1007.1, R1008.1, R1009.1, R1010.1, R1011.1, R1012.1, R1037.1, R1038.1, R1039.1, R1040.1, R1101.1, R1102.1, R1103.1, R1104.1, R1105.1, R1106.1, R1107.1, R1108.1, R1109.1, R1110.1, R1111.1, R1112.1, R1137.1, R1138.1, R1139.1, R1140.1, R1141.1, R1142.1, R1143.1, R1144.1, R1201.1, R1202.1, R1203.1, R1204.1, R1205.1, R1206.1, R1207.1, R1208.1, R1209.1, R1210.1, R1211.1, R1212.1, R1237.1, R1238.1, R1239.1, R1240.1, R1241.1, R1242.1, R1243.1, R1244.1, R1301.1, R1302.1, R1303.1, R1304.1, R1305.1, R1306.1, R1307.1, R1308.1, R1309.1, R1310.1, R1311.1, R1312.1, R1337.1, R1338.1, R1339.1, R1340.1, R1341.1, R1342.1, R1343.1, R1344.1, R1401.1, R1402.1, R1403.1, R1404.1, R1405.1, R1406.1, R1407.1, R1408.1, R1409.1, R1410.1, R1411.1, R1412.1, R1437.1, R1438.1, R1439.1, R1440.1, R1441.1, R1442.1, R1443.1, R1444.1, R1501.1, R1502.1, R1503.1, R1504.1, R1505.1, R1506.1, R1507.1, R1508.1, R1509.1, R1510.1, R1511.1, R1512.1, R1537.1, R1538.1, R1539.1, R1540.1, R1541.1, R1542.1, R1543.1, R1544.1, R1601.1, R1602.1, R1603.1, R1604.1, R1605.1, R1606.1, R1607.1, R1608.1, R1609.1, R1610.1, R1611.1, R1612.1, R1637.1, R1638.1, R1639.1, R1640.1, R1641.1, R1642.1, R1643.1, R1644.1, R1701.1, R1702.1, R1703.1, R1704.1, R1705.1, R1706.1, R1707.1, R1708.1, R1709.1, R1710.1, R1711.1, R1712.1, R1737.1, R1738.1, R1739.1, R1740.1, R1741.1, R1742.1, R1743.1, R1744.1, R1801.1, R1802.1, R1803.1, R1804.1, R1805.1, R1806.1, R1807.1, R1808.1, R1809.1, R1810.1, R1811.1, R1812.1, R1837.1, R1838.1, R1839.1, R1840.1, R1841.1, R1842.1, R1843.1, R1844.1, R1901.1, R1902.1, R1903.1, R1904.1, R1905.1, R1906.1, R1907.1, R1908.1, R1909.1, R1910.1, R1911.1, R1912.1, R1937.1, R1938.1, R1939.1, R1940.1

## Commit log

2017-09-06 Schematic and layout complete and ready for review
2017-09-06 Pushing again. I may have missed some files the first time. To be clear, the schematic and layout are complete and ready for review.
